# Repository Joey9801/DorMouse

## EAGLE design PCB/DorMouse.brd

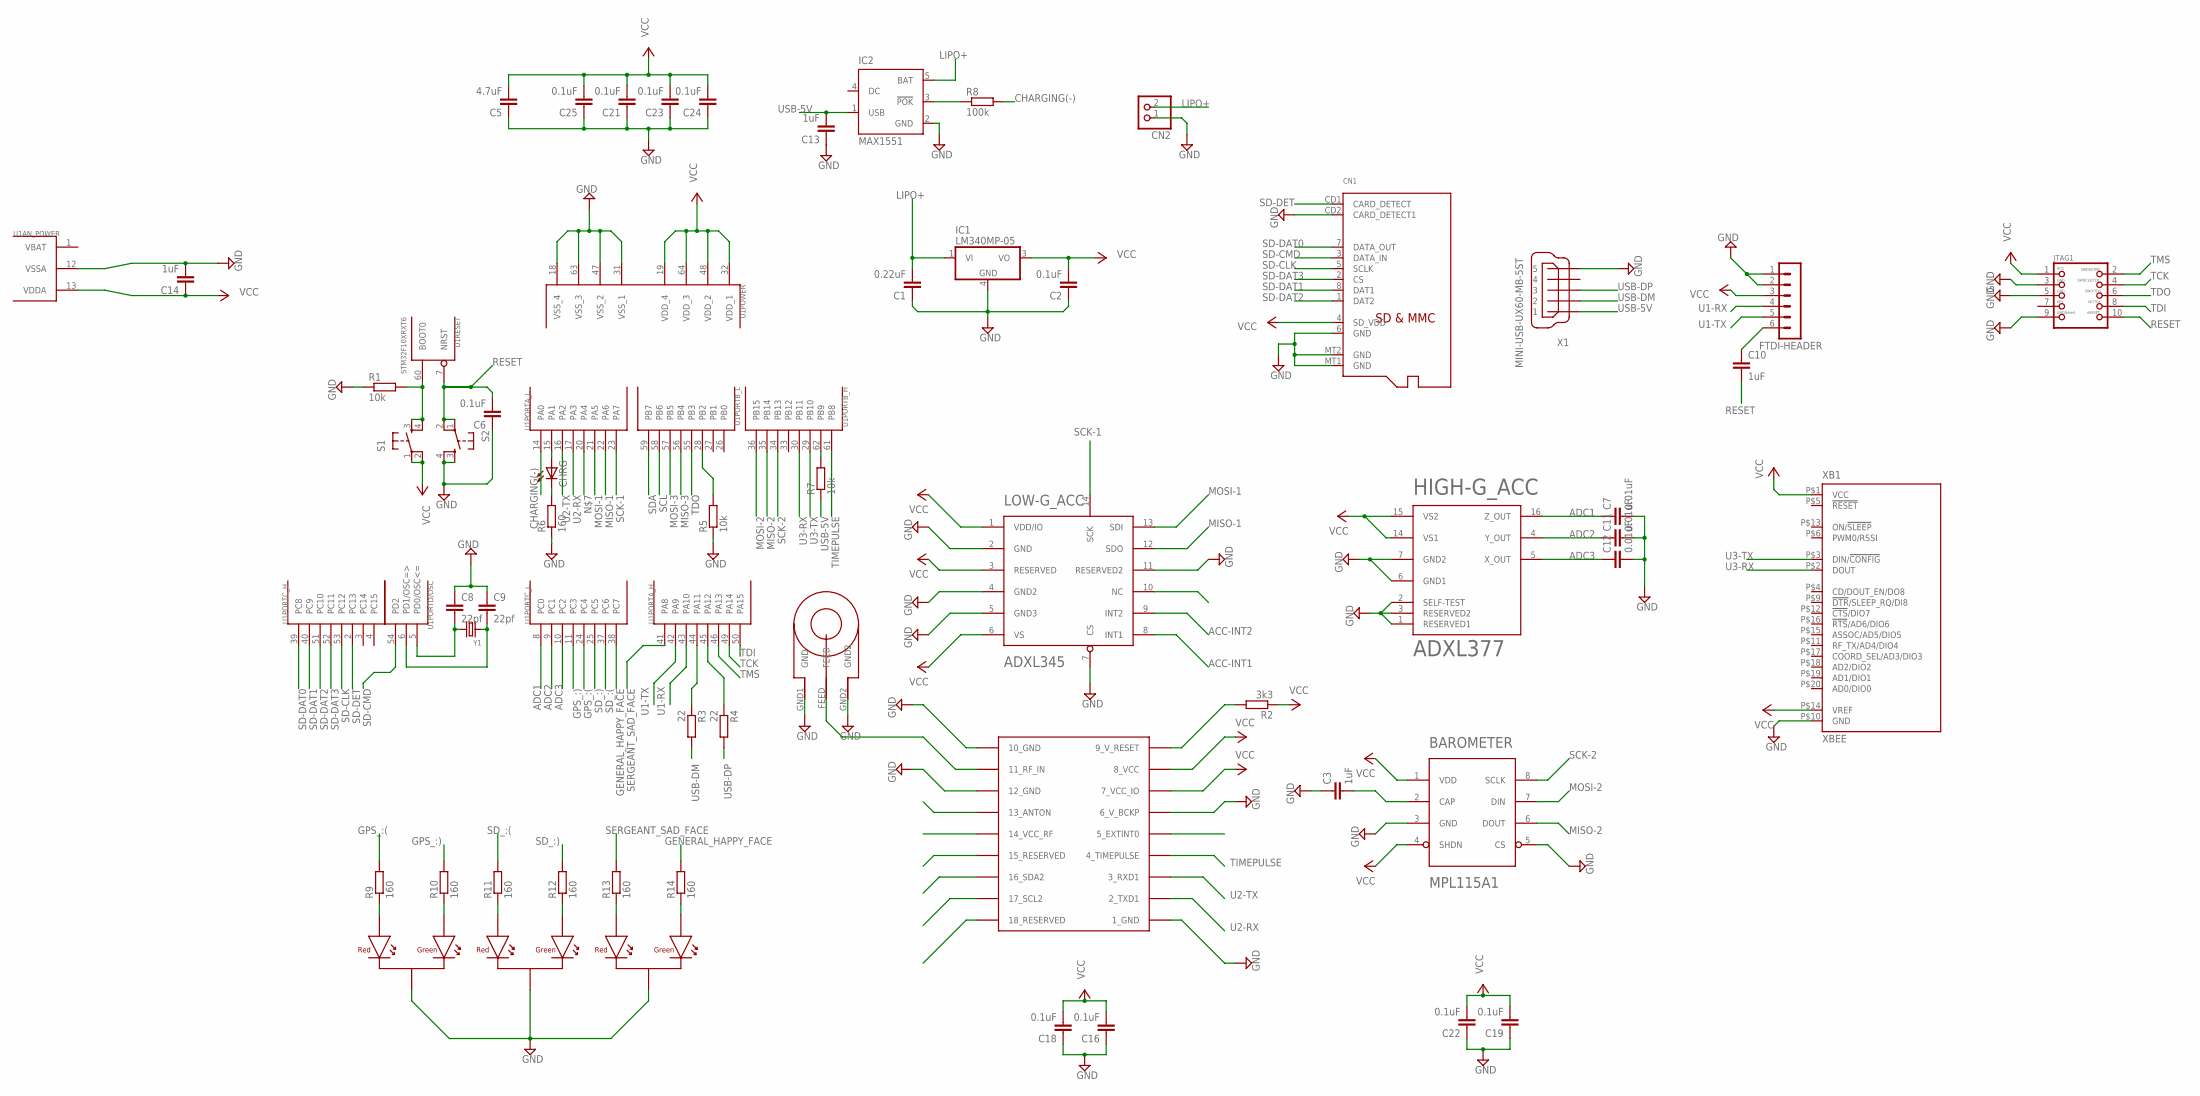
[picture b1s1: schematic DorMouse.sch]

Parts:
BAROMETER: MPL115A1; LGA-8
C1: 0.22uF; C0402
C2, C6, C16, C18, C19, C21, C22, C23, C24, C25: 0.1uF; C0402
C3, C10, C13, C14: 1uF; C0402
C5: 4.7uF; C0402
C7, C11, C12: 0.01uF; C0402
C8, C9: 22pf; C0402
CHRG: LEDCHIPLED_0603; CHIPLED_0603
CN1: MICROSD
CN2: JST_2PINSH2; JSTSH2
FTDI-HEADER: MA06-1
GENERAL: RED-GREEN_LED; SOT23
GPS: UBLOX_MAX-6
GPS-LED: RED-GREEN_LED; SOT23
HIGH-G_ACC: ADXL377; LFCSP-16
IC1: LM340MP-05; SOT223
IC2: MAX1551; SOT23-5L
JTAG1: JTAG-CORTEXM3; 2X05_1.27MM_SMT
LOW-G_ACC: ADXL345; LGA-14
R1, R5, R7: 10k; R0402
R2: 3k3; R0402
R3, R4: 22; R0402
R6, R9, R10, R11, R12, R13, R14: 160; R0402
R8: 100k; R0402
S1, S2: TAC_SWITCHSMD; TACTILE_SWITCH_SMD
SD-LED: RED-GREEN_LED; SOT23
U1: STM32F10XRXT6; TQFP64
U$1: SARANTEL-SR1202
X1: MINI-USB-UX60-MB-5ST; UX60-MB-5ST
XB1: XBEE
Y1: CRYSTALSMD; HC49UP

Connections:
ACC-INT1: LOW-G_ACC.8 (INT1)
ACC-INT2: LOW-G_ACC.9 (INT2)
ADC1: C7.1, HIGH-G_ACC.16 (Z_OUT), U1.8 (PC0)
ADC2: C11.1, HIGH-G_ACC.4 (Y_OUT), U1.9 (PC1)
ADC3: C12.1, HIGH-G_ACC.5 (X_OUT), U1.10 (PC2)
BOOT1: R5.2, U1.28 (PB2)
CHARGING(-): R8.2, U1.14 (PA0)
GENERAL_HAPPY_FACE: R14.2, U1.38 (PC7)
GND: BAROMETER.3 (GND), BAROMETER.5 (CS), C1.1, C2.1, C3.1, C5.1, C6.1, C7.2, C8.1, C9.1, C11.2, C12.2, C13.1, C14.2, C16.1, C18.1, C19.1, C21.1, C22.1, C23.1, C24.1, C25.1, CN1.6 (GND), CN1.CD2 (CARD_DETECT1), CN1.MT1 (GND), CN1.MT2 (GND), CN2.1, FTDI-HEADER.1, FTDI-HEADER.2, GENERAL.3 (CATHODE), GPS.1_GND, GPS.6_V_BCKP, GPS.10_GND, GPS.12_GND, GPS-LED.3 (CATHODE), HIGH-G_ACC.1 (RESERVED1), HIGH-G_ACC.2 (SELF-TEST), HIGH-G_ACC.3 (RESERVED2), HIGH-G_ACC.6 (GND1), HIGH-G_ACC.7 (GND2), IC1.4 (GND), IC2.2 (GND), JTAG1.3, JTAG1.5, JTAG1.9, LOW-G_ACC.2 (GND), LOW-G_ACC.4 (GND2), LOW-G_ACC.5 (GND3), LOW-G_ACC.7 (CS), LOW-G_ACC.11 (RESERVED2), R1.1, R5.1, R6.1, S2.3, S2.4, SD-LED.3 (CATHODE), U1.12 (VSSA), U1.18 (VSS_4), U1.31 (VSS_1), U1.47 (VSS_2), U1.63 (VSS_3), U$1.GND1 (GND), U$1.GND2, X1.5, XB1.P$10 (GND)
GPS_:(: R9.2, U1.24 (PC4)
GPS_:): R10.2, U1.11 (PC3)
LIPO+: C1.2, CN2.2, IC1.1 (VI), IC2.5 (BAT)
MISO-1: LOW-G_ACC.12 (SDO), U1.22 (PA6)
MISO-2: BAROMETER.6 (DOUT), U1.35 (PB14)
MISO-3: U1.56 (PB4)
MOSI-1: LOW-G_ACC.13 (SDI), U1.21 (PA5)
MOSI-2: BAROMETER.7 (DIN), U1.36 (PB15)
MOSI-3: U1.57 (PB5)
unnamed: R1.2, S1.3, S1.4, U1.60 (BOOT0)
unnamed: BAROMETER.2 (CAP), C3.2
unnamed: R3.1, U1.44 (PA11)
unnamed: C9.2, U1.6 (PD1/OSC=>), Y1.1
unnamed: R4.1, U1.45 (PA12)
unnamed: CHRG.A, U1.15 (PA1)
unnamed: CHRG.C, R6.2
unnamed: IC2.3 (!POK), R8.1
unnamed: C8.2, U1.5 (PD0/OSC<=), Y1.2
unnamed: GPS.9_V_RESET, R2.2
unnamed: GPS-LED.1 (RED-ANODE), R9.1
unnamed: GPS.11_RF_IN, U$1.FEED
unnamed: C10.1, FTDI-HEADER.6
unnamed: R7.2, U1.62 (PB9)
unnamed: GPS-LED.2 (GREEN-ANODE), R10.1
unnamed: R11.1, SD-LED.1 (RED-ANODE)
unnamed: R12.1, SD-LED.2 (GREEN-ANODE)
unnamed: GENERAL.1 (RED-ANODE), R13.1
unnamed: GENERAL.2 (GREEN-ANODE), R14.1
RESET: C6.2, C10.2, JTAG1.10, S2.1, S2.2, U1.7 (NRST)
SCK-1: LOW-G_ACC.14 (SCK), U1.23 (PA7)
SCK-2: BAROMETER.8 (SCLK), U1.34 (PB13)
SCL: U1.58 (PB6)
SD-CLK: CN1.5 (SCLK), U1.53 (PC12)
SD-CMD: CN1.3 (DATA_IN), U1.54 (PD2)
SD-DAT0: CN1.7 (DATA_OUT), U1.39 (PC8)
SD-DAT1: CN1.8 (DAT1), U1.40 (PC9)
SD-DAT2: CN1.1 (DAT2), U1.51 (PC10)
SD-DAT3: CN1.2 (CS), U1.52 (PC11)
SD-DET: CN1.CD1 (CARD_DETECT), U1.2 (PC13)
SDA: U1.59 (PB7)
SD_:(: R11.2, U1.37 (PC6)
SD_:): R12.2, U1.25 (PC5)
SERGEANT_SAD_FACE: R13.2, U1.41 (PA8)
TCK: JTAG1.4, U1.49 (PA14)
TDI: JTAG1.8, U1.50 (PA15)
TDO: JTAG1.6, U1.55 (PB3)
TIMEPULSE: GPS.4_TIMEPULSE, U1.61 (PB8)
TMS: JTAG1.2, U1.46 (PA13)
U1-RX: FTDI-HEADER.4, U1.43 (PA10)
U1-TX: FTDI-HEADER.5, U1.42 (PA9)
U2-RX: GPS.2_TXD1, U1.17 (PA3)
U2-TX: GPS.3_RXD1, U1.16 (PA2)
U3-RX: U1.30 (PB11), XB1.P$2 (DOUT)
U3-TX: U1.29 (PB10), XB1.P$3 (DIN/!CONFIG)
USB-5V: C13.2, IC2.1 (USB), R7.1, X1.1
USB-DM: R3.2, X1.2
USB-DP: R4.2, X1.3
VBAT: U1.1 (VBAT)
VCC: BAROMETER.1 (VDD), BAROMETER.4 (SHDN), C2.2, C5.2, C14.1, C16.2, C18.2, C19.2, C21.2, C22.2, C23.2, C24.2, C25.2, CN1.4 (SD_VDD), FTDI-HEADER.3, GPS.7_VCC_IO, GPS.8_VCC, HIGH-G_ACC.14 (VS1), HIGH-G_ACC.15 (VS2), IC1.3 (VO), JTAG1.1, LOW-G_ACC.1 (VDD/IO), LOW-G_ACC.3 (RESERVED), LOW-G_ACC.6 (VS), R2.1, S1.1, S1.2, U1.13 (VDDA), U1.19 (VDD_4), U1.32 (VDD_1), U1.48 (VDD_2), U1.64 (VDD_3), XB1.P$1 (VCC), XB1.P$14 (VREF)

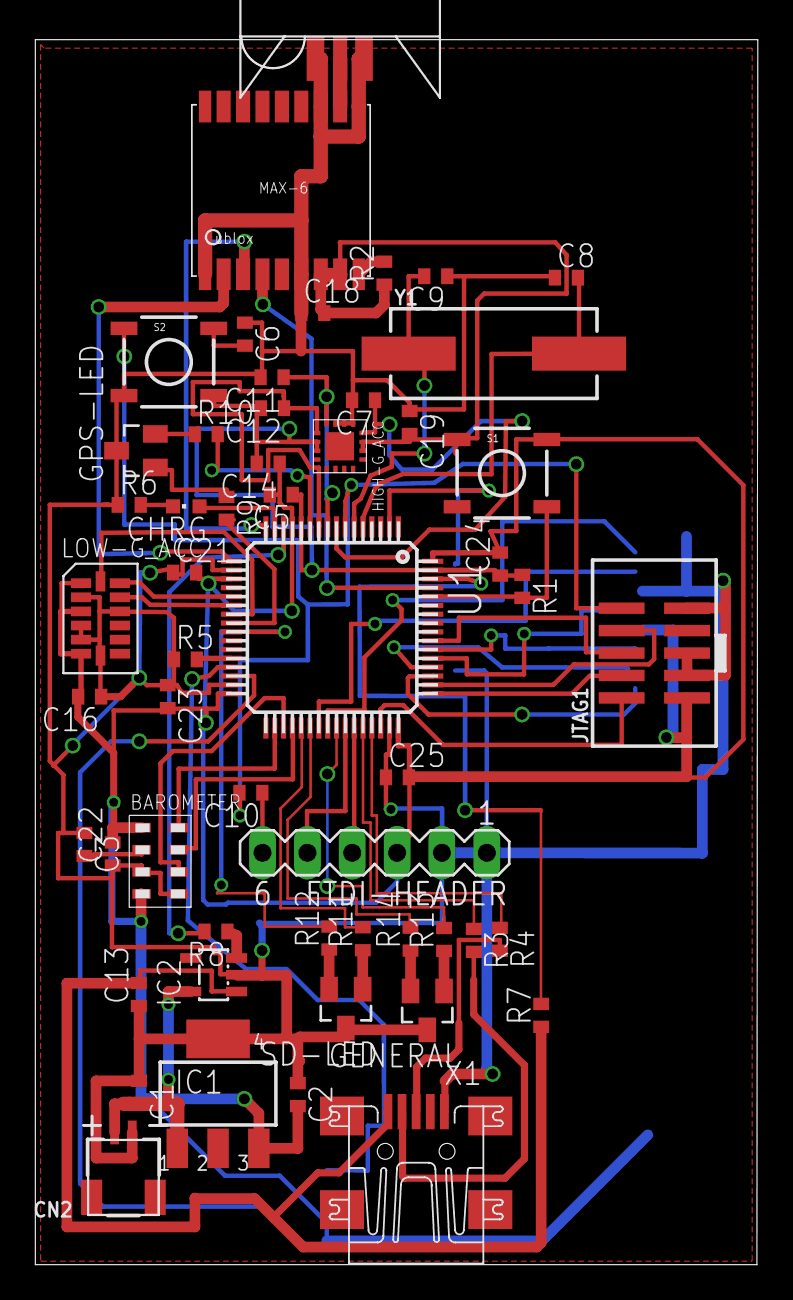
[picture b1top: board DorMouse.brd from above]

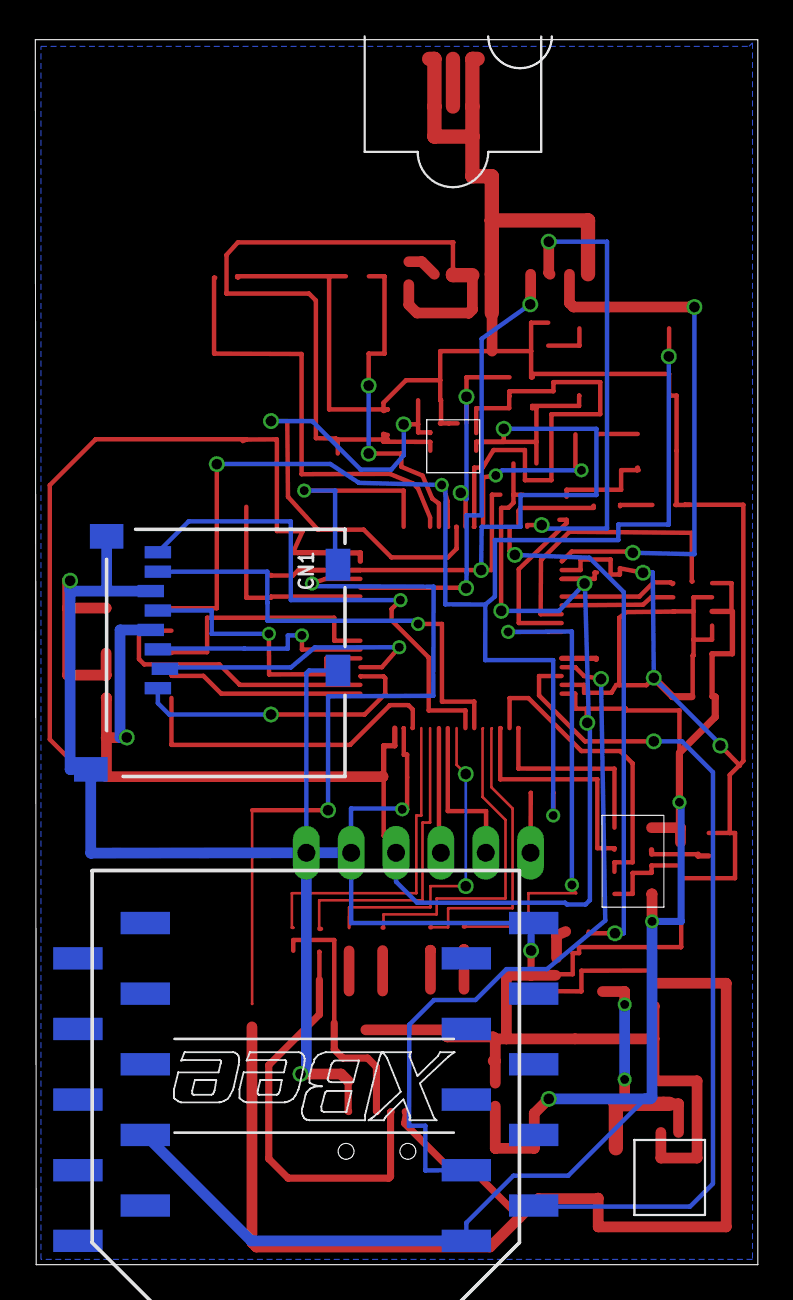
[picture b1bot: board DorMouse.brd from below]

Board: 2 copper layers, 40.9 x 69.4 mm, 56 parts (2 on the bottom side), 61 nets.

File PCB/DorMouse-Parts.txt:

Part,Value,Device,Package,Library,Sheet

BAROMETER,MPL115A1,MPL115A1,LGA-8,Swallow,1
C1,0.22uF,C-EUC0402,C0402,rcl,1
C2,0.1uF,C-EUC0402,C0402,rcl,1
C3,1uF,C-EUC0402,C0402,rcl,1
C4,10nF,C-EUC0402,C0402,rcl,1
C5,4.7uF,C-EUC0402,C0402,rcl,1
C6,0.1uF,C-EUC0402,C0402,rcl,1
C7,0.01uF,C-EUC0402,C0402,rcl,1
C8,22pf,C-EUC0402,C0402,rcl,1
C9,22pf,C-EUC0402,C0402,rcl,1
C10,1uF,C-EUC0402,C0402,rcl,1
C11,0.01uF,C-EUC0402,C0402,rcl,1
C12,0.01uF,C-EUC0402,C0402,rcl,1
C14,1uF,C-EUC0402,C0402,rcl,1
C16,0.1uF,C-EUC0402,C0402,rcl,1
C18,0.1uF,C-EUC0402,C0402,rcl,1
C19,0.1uF,C-EUC0402,C0402,rcl,1
C21,0.1uF,C-EUC0402,C0402,rcl,1
C22,0.1uF,C-EUC0402,C0402,rcl,1
C23,0.1uF,C-EUC0402,C0402,rcl,1
C24,0.1uF,C-EUC0402,C0402,rcl,1
C25,0.1uF,C-EUC0402,C0402,rcl,1
CHRG,LEDCHIPLED_0603,CHIPLED_0603,led,1
CN1,MICROSD,MICROSD,microbuilder,1
CN2,JST_2PINSH2,JSTSH2,microbuilder,1
FTDI-HEADER,MA06-1,MA06-1,con-lstb,1
GENERAL,RED-GREEN_LED,RED-GREEN_LED,SOT23,DorMouse,1
GPS,UBLOX_MAX-6,UBLOX_MAX-6,UBLOX_MAX-6,Ava,1
GPS-LED,RED-GREEN_LED,RED-GREEN_LED,SOT23,DorMouse,1
HIGH-G_ACC,ADXL377,ADXL377,LFCSP-16,Swallow,1
IC1,LM340MP-05,LM340MP-05,SOT223,linear,1
IC2,MAX1551,MAX1551,SOT23-5L,maxim,1
JTAG1,JTAG-CORTEXM3,2X05_1.27MM_SMT,microbuilder,1
LOW-G_ACC,ADXL345,ADXL345,LGA-14,Swallow,1
R1,10k,R-EU_R0402,R0402,rcl,1
R2,3k3,R-EU_R0402,R0402,rcl,1
R3,22,R-EU_R0402,R0402,rcl,1
R4,22,R-EU_R0402,R0402,rcl,1
R5,10k,R-EU_R0402,R0402,rcl,1
R6,160,R-EU_R0402,R0402,rcl,1
R7,10k,R-EU_R0402,R0402,rcl,1
R9,160,R-EU_R0402,R0402,rcl,1
R10,160,R-EU_R0402,R0402,rcl,1
R11,160,R-EU_R0402,R0402,rcl,1
R12,160,R-EU_R0402,R0402,rcl,1
R13,160,R-EU_R0402,R0402,rcl,1
R14,160,R-EU_R0402,R0402,rcl,1
S1,TAC_SWITCHSMD,TACTILE_SWITCH_SMD,SparkFun,1
S2,TAC_SWITCHSMD,TACTILE_SWITCH_SMD,SparkFun,1
SD-LED,RED-GREEN_LED,RED-GREEN_LED,SOT23,DorMouse,1
U$1,SARANTEL-SR1202,SARANTEL-SR1202,SARANTEL-SR1202,Ava,1
U1,STM32F10XRXT6,STM32F10XRXT6,TQFP64,stm32,1
X1,MINI-USB-UX60-MB-5ST,MINI-USB-UX60-MB-5ST,UX60-MB-5ST,con-hirose,1
XB1,XBEE,XBEE,XBEE,Swallow,1
Y1,CRYSTALSMD,HC49UP,microbuilder,1

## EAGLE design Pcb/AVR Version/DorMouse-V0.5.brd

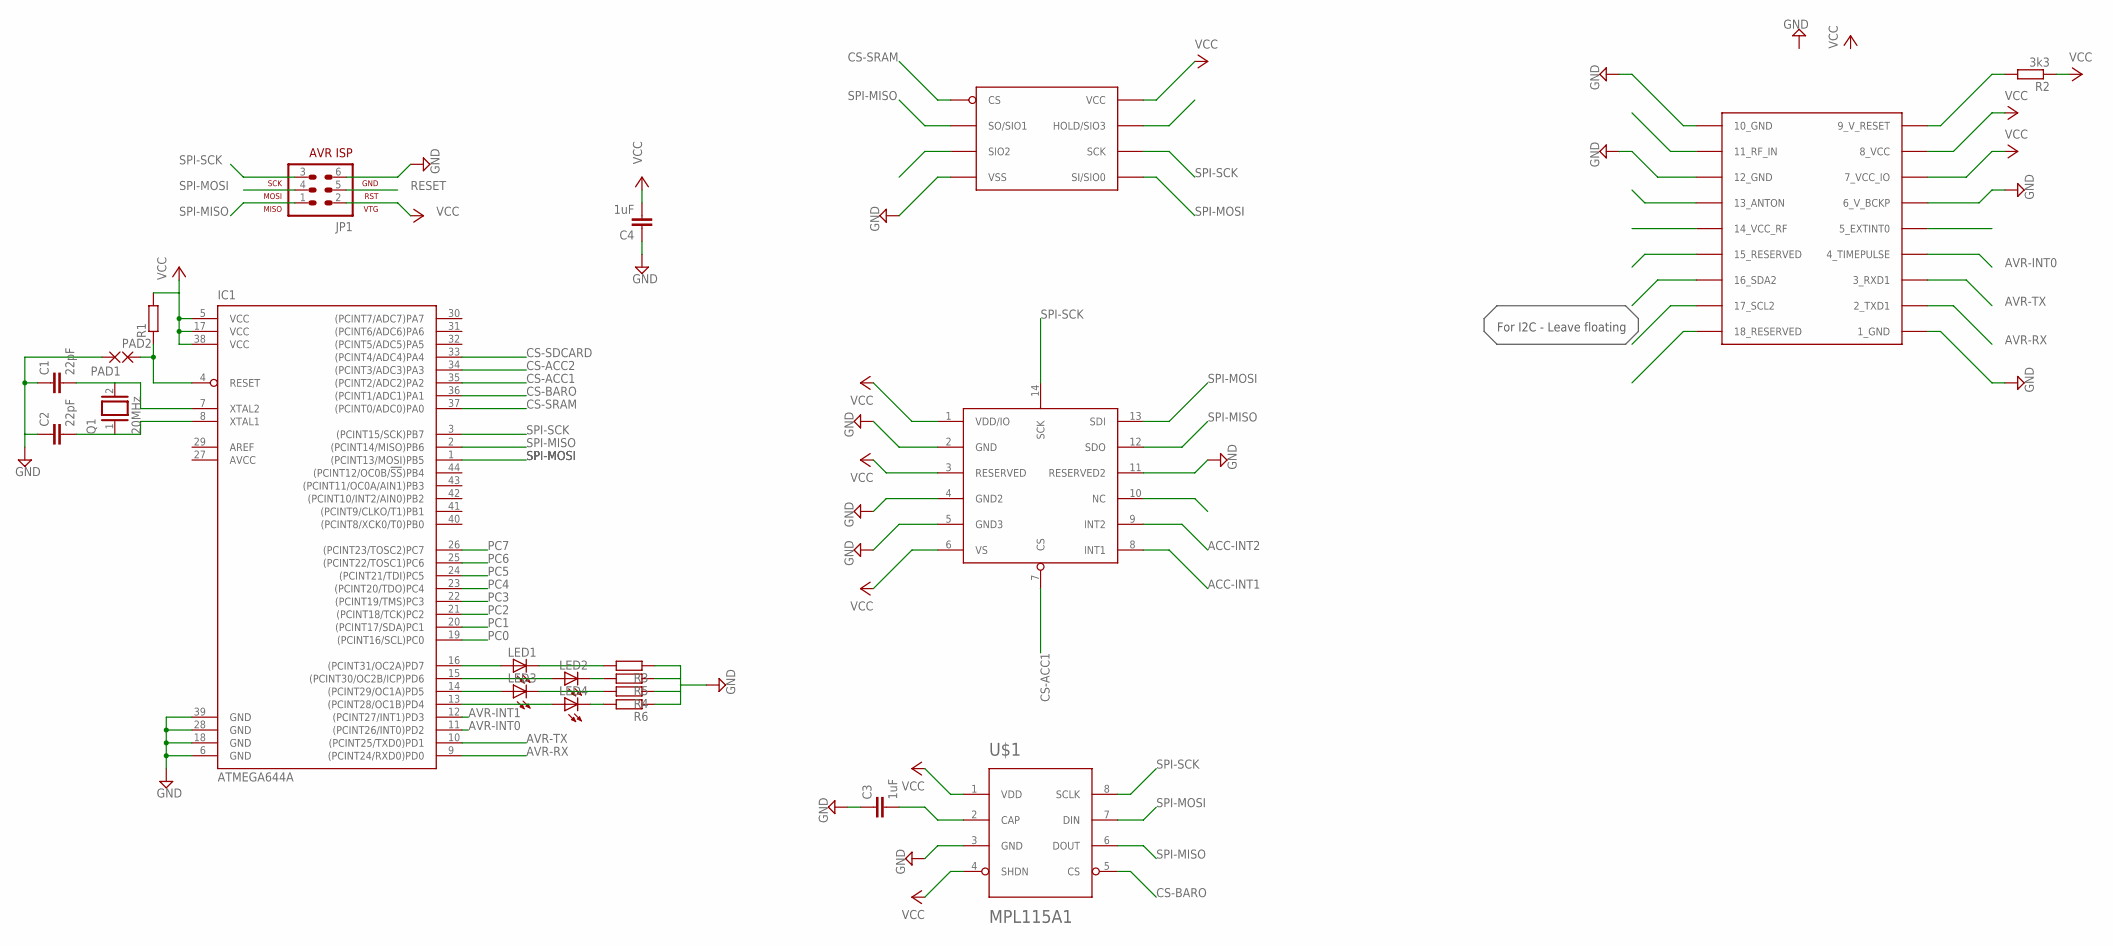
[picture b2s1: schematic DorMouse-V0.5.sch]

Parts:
C1, C2: 22pF; C0402
C3, C4: 1uF; C0402
IC1: ATMEGA644A; TQFP44
JP1: AVR-ISP-6
LED1, LED2, LED3, LED4: LEDCHIP-LED0603; CHIP-LED0603
PAD1, PAD2: SMD2; SMD1,27-2,54
Q1: 20MHz; QS
R1, R3, R4, R5, R6: R-EU_R0402; R0402
R2: 3k3; R0402
SPI-SRAM: 23LC1024; SOIC8
U$1: MPL115A1; LGA-8
U$2: ADXL345; LGA-14
U$3: UBLOX_MAX-6

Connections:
ACC-INT1: U$2.8 (INT1)
ACC-INT2: U$2.9 (INT2)
AVCC: IC1.27 (AVCC)
AVR-INT0: IC1.11 ((PCINT26/INT0)PD2), U$3.4_TIMEPULSE
AVR-INT1: IC1.12 ((PCINT27/INT1)PD3)
AVR-RX: IC1.9 ((PCINT24/RXD0)PD0), U$3.2_TXD1
AVR-TX: IC1.10 ((PCINT25/TXD0)PD1), U$3.3_RXD1
CS-ACC1: IC1.35 ((PCINT2/ADC2)PA2), U$2.7 (CS)
CS-ACC2: IC1.34 ((PCINT3/ADC3)PA3)
CS-BARO: IC1.36 ((PCINT1/ADC1)PA1), U$1.5 (CS)
CS-SRAM: IC1.37 ((PCINT0/ADC0)PA0), SPI-SRAM.1 (CS)
GND: C1.1, C2.1, C3.1, C4.1, IC1.6 (GND), IC1.18 (GND), IC1.28 (GND), IC1.39 (GND), JP1.6, PAD1.1, R3.1, R4.1, R5.1, R6.1, SPI-SRAM.4 (VSS), U$1.3 (GND), U$2.2 (GND), U$2.4 (GND2), U$2.5 (GND3), U$2.11 (RESERVED2), U$3.1_GND, U$3.6_V_BCKP, U$3.10_GND, U$3.12_GND
unnamed: C1.2, IC1.7 (XTAL2), Q1.2
unnamed: C2.2, IC1.8 (XTAL1), Q1.1
unnamed: C3.2, U$1.2 (CAP)
unnamed: IC1.16 ((PCINT31/OC2A)PD7), LED1.A
unnamed: IC1.15 ((PCINT30/OC2B/ICP)PD6), LED2.A
unnamed: IC1.14 ((PCINT29/OC1A)PD5), LED3.A
unnamed: IC1.13 ((PCINT28/OC1B)PD4), LED4.A
unnamed: LED1.C, R3.2
unnamed: R2.2, U$3.9_V_RESET
unnamed: LED2.C, R5.2
unnamed: LED3.C, R4.2
unnamed: LED4.C, R6.2
PC0: IC1.19 ((PCINT16/SCL)PC0)
PC1: IC1.20 ((PCINT17/SDA)PC1)
PC2: IC1.21 ((PCINT18/TCK)PC2)
PC3: IC1.22 ((PCINT19/TMS)PC3)
PC4: IC1.23 ((PCINT20/TDO)PC4)
PC5: IC1.24 ((PCINT21/TDI)PC5)
PC6: IC1.25 ((PCINT22/TOSC1)PC6)
PC7: IC1.26 ((PCINT23/TOSC2)PC7)
RESET: IC1.4 (RESET), JP1.5, PAD2.1, R1.1
SPI-MISO: IC1.2 ((PCINT14/MISO)PB6), JP1.1, SPI-SRAM.2 (SO/SIO1), U$1.6 (DOUT), U$2.12 (SDO)
SPI-MOSI: IC1.1 ((PCINT13/MOSI)PB5), JP1.4, SPI-SRAM.5 (SI/SIO0), U$1.7 (DIN), U$2.13 (SDI)
SPI-SCK: IC1.3 ((PCINT15/SCK)PB7), JP1.3, SPI-SRAM.6 (SCK), U$1.8 (SCLK), U$2.14 (SCK)
VCC: C4.2, IC1.5 (VCC), IC1.17 (VCC), IC1.38 (VCC), JP1.2, R1.2, R2.1, SPI-SRAM.8 (VCC), U$1.1 (VDD), U$1.4 (SHDN), U$2.1 (VDD/IO), U$2.3 (RESERVED), U$2.6 (VS), U$3.7_VCC_IO, U$3.8_VCC

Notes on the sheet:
For I2C - Leave floating

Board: 2 copper layers, 23 parts (1 on the bottom side), 24 nets, no tracks yet.

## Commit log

2012-11-19 Schematic V1.0
2012-11-19 Revert "Schematic V1.0"
    This reverts commit 5b7367a116f23bcf11c69161516df83586e723bb.
2012-11-20 Finished rev1.0 schematic
2012-11-20 V1.1 Schematic update
2012-11-21 pcb v1
2012-11-22 Multiple fixes to schematic, addition of pdf, clean board and partslist.
    Ava library fixed: open and save, then it works (?)
    Ran ERC: complained about missing joins and signals near each other without
    being connected. Discovered one case where something that should be
    conected was not. Fixed, then as a precautionary measure, added join
    dots everywhere (sorry).
    Wrong antenna footprint. Swapped.
2012-11-22 Add resistor and cap, reverse ADC connections. Warning: desync
2012-11-22 Sync older board with schematic
2012-11-23 Most of the pcb done
2012-11-23 PCB r1 - Finished
    Al wires routed
    No overlaps
    Total size - 41x70mm
2012-11-23 Fix DRC errors
2012-11-23 Approve errors. Add polygon Pour
2012-11-23 Gerber png and pdf all the things
2012-11-23 microbuilder library

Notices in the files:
parts and their libraries:
microbuilder: This work is placed in the public domain, and may be freely used for commercial and non-commercial work with the following conditions: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
SparkFun: Licensing: CC v3.0 Share-Alike You are welcome to use this library for commercial purposes.
